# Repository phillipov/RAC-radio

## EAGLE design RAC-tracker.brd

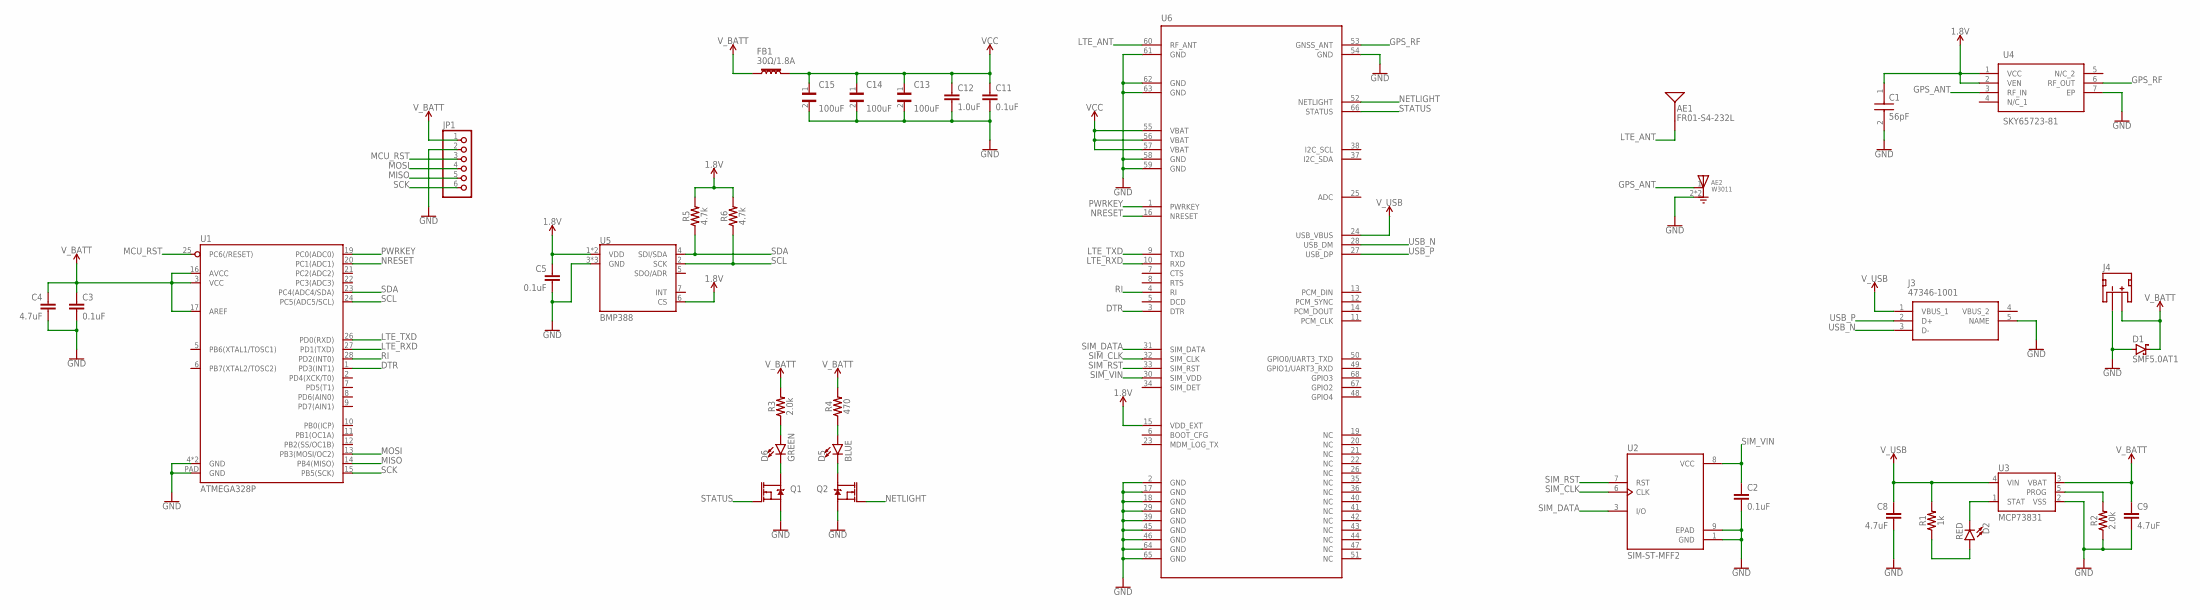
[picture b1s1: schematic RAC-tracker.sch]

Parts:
AE1: FR01-S4-232L; FR01-S4-232
AE2: W3011; XDCR_W3011
C1: 56pF; CAPC1608X90N
C2, C3, C5, C11: 0.1uF; 0603
C4, C8, C9: 4.7uF; 0603
C12: 1.0uF; 0603
C13, C14, C15: 100uF; CAPC3216X180N
D1: SMF5.0AT1; SOD123FL
D2: RED; LED-0603
D5: BLUE; LED-0603
D6: GREEN; LED-0603
FB1: 30Ω/1.8A; 0603
J3: 47346-1001; 47346-0001
J4: JST_2MM_MALE; JST-2-SMD
JP1: PINHD-1X6; 1X06
Q1, Q2: 220mA/50V/3.5Ω; SOT23-3
R1: 1k; 0603
R2, R3: 2.0k; 0603
R4: 470; 0603
R5, R6: 4.7k; 0603
U1: ATMEGA328P; VQFN-28
U2: SIM-ST-MFF2; PSON127P500X600X82-9N
U3: MCP73831; SOT23-5
U4: SKY65723-81; SKY6572381
U5: BMP388; LGA-10(2X2)
U6: SIM7000

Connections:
1.8V: C1.1, C5.1, R5.2, R6.2, U4.1 (VCC), U4.2 (VEN), U5.1 (VDD), U5.6 (CS), U5.10 (VDD), U6.15 (VDD_EXT)
DTR: U1.1 (PD3(INT1)), U6.3 (DTR)
GND: AE2.2 (GND), AE2.3 (GND), C1.2, C2.2, C3.2, C4.2, C5.2, C8.2, C9.2, C11.2, C12.2, C13.2, C14.2, C15.2, D1.A, J3.5 (NAME), J4.1 (-), JP1.2, Q1.2 (S), Q2.2 (S), R2.1, U1.4 (GND), U1.18 (GND), U1.PAD (GND), U2.1 (GND), U2.9 (EPAD), U3.2 (VSS), U4.7 (EP), U5.3 (GND), U5.8 (GND), U5.9 (GND), U6.2 (GND), U6.17 (GND), U6.18 (GND), U6.29 (GND), U6.39 (GND), U6.45 (GND), U6.46 (GND), U6.54 (GND), U6.58 (GND), U6.59 (GND), U6.61 (GND), U6.62 (GND), U6.63 (GND), U6.64 (GND), U6.65 (GND)
GPS_ANT: AE2.1 (FEED), U4.3 (RF_IN)
GPS_RF: U4.6 (RF_OUT), U6.53 (GNSS_ANT)
LED_NET_A: D5.A, R4.1
LED_NET_C: D5.C, Q2.3 (D)
LED_STAT_A: D6.A, R3.1
LED_STAT_C: D6.C, Q1.3 (D)
LTE_ANT: AE1.2, U6.60 (RF_ANT)
LTE_RXD: U1.27 (PD1(TXD)), U6.10 (RXD)
LTE_TXD: U1.26 (PD0(RXD)), U6.9 (TXD)
MCU_RST: JP1.3, U1.25 (PC6(/RESET))
MISO: JP1.5, U1.14 (PB4(MISO))
MOSI: JP1.4, U1.13 (PB3(MOSI/OC2))
NETLIGHT: Q2.1 (G), U6.52 (NETLIGHT)
NRESET: U1.20 (PC1(ADC1)), U6.16 (NRESET)
PROG: R2.2, U3.5 (PROG)
PWRKEY: U1.19 (PC0(ADC0)), U6.1 (PWRKEY)
RI: U1.28 (PD2(INT0)), U6.4 (RI)
SCK: JP1.6, U1.15 (PB5(SCK))
SCL: R6.1, U1.24 (PC5(ADC5/SCL)), U5.2 (SCK)
SDA: R5.1, U1.23 (PC4(ADC4/SDA)), U5.4 (SDI/SDA)
SIM_CLK: U2.6 (CLK), U6.32 (SIM_CLK)
SIM_DATA: U2.3 (I/O), U6.31 (SIM_DATA)
SIM_RST: U2.7 (RST), U6.33 (SIM_RST)
SIM_VIN: C2.1, U2.8 (VCC), U6.30 (SIM_VDD)
STAT: D2.C, U3.1 (STAT)
STATUS: Q1.1 (G), U6.66 (STATUS)
STAT_AN: D2.A, R1.1
USB_N: J3.3 (D-), U6.28 (USB_DM)
USB_P: J3.2 (D+), U6.27 (USB_DP)
VCC: C11.1, C12.1, C13.1, C14.1, C15.1, FB1.2, U6.55 (VBAT), U6.56 (VBAT), U6.57 (VBAT)
V_BATT: C3.1, C4.1, C9.1, D1.C, FB1.1, J4.2 (+), JP1.1, R3.2, R4.2, U1.3 (VCC), U1.16 (AVCC), U1.17 (AREF), U3.3 (VBAT)
V_USB: C8.1, J3.1 (VBUS_1), R1.2, U3.4 (VIN), U6.24 (USB_VBUS)

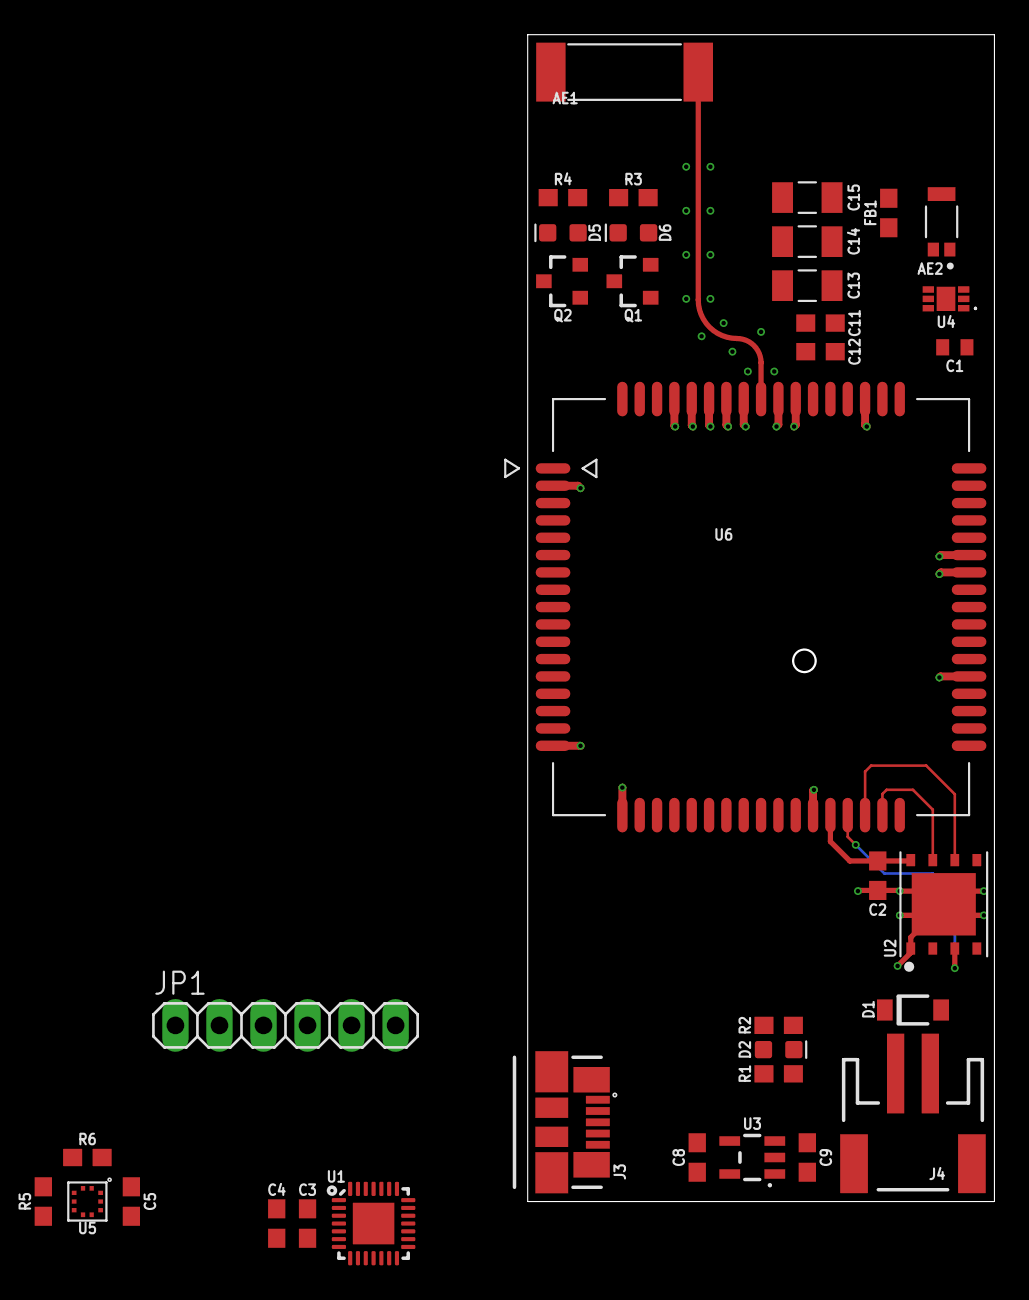
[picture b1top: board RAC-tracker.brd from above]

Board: 4 copper layers, 26.9 x 67.3 mm, 36 parts (0 on the bottom side), 35 nets.

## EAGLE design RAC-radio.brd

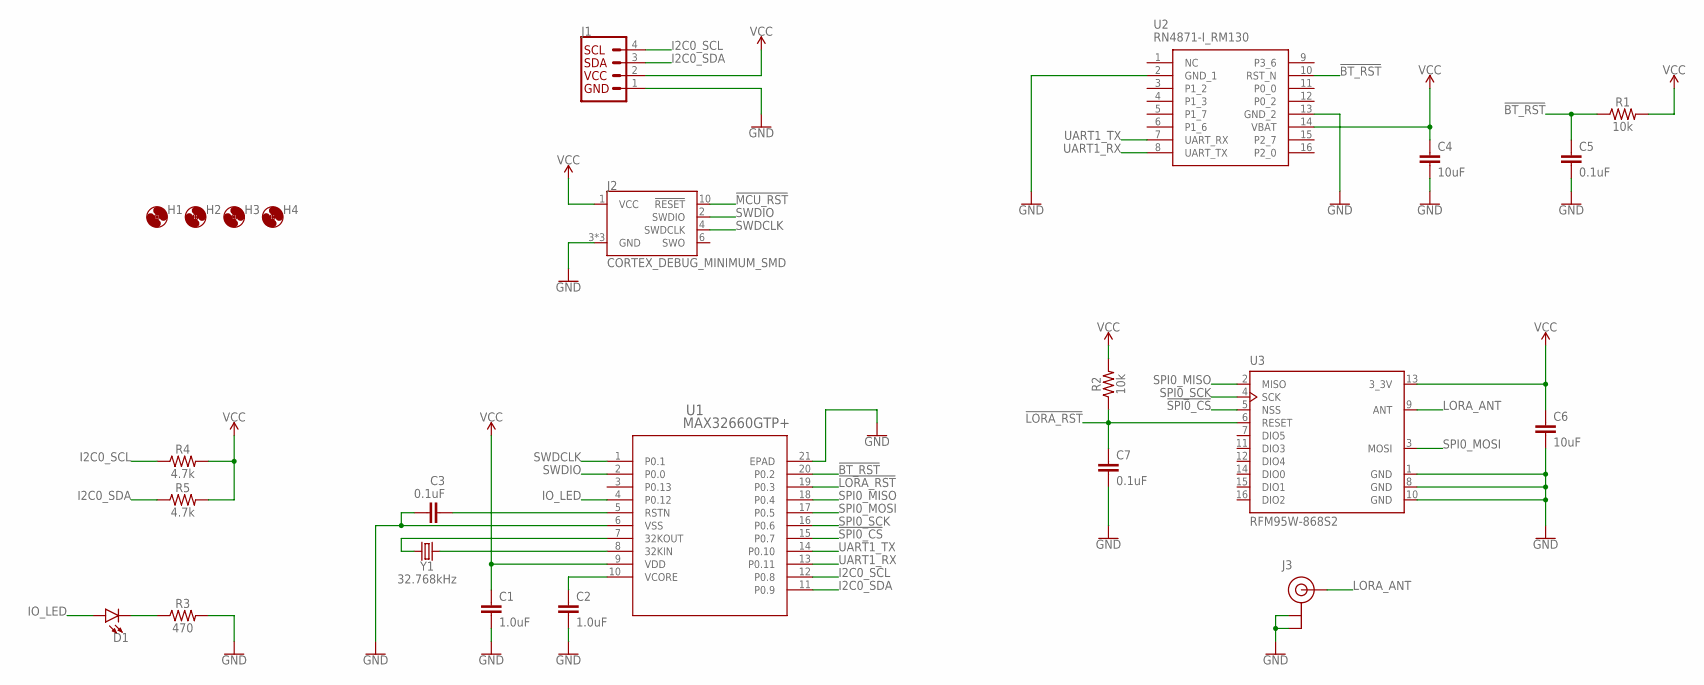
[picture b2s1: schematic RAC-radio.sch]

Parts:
C1, C2: 1.0uF; 0603
C3, C5, C7: 0.1uF; 0603
C4, C6: 10uF; 0603
D1: LED0603; LED-0603
H1, H2, H3, H4: MOUNT-HOLE2.8; 2,8
J1: QWIIC_CONNECTORJS-1MM; JST04_1MM_RA
J2: CORTEX_DEBUG_MINIMUM_SMD; SAMTECH_FTSH-105-01
J3: U.FL
R1, R2: 10k; 0603
R3: 470; 0603
R4, R5: 4.7k; 0603
U1: MAX32660GTP+; 21-0139V_T2044+5
U2: RN4871-I_RM130; RN4871
U3: RFM95W-868S2; XCVR_RFM95W-868S2
Y1: 32.768kHz; CRYSTAL-SMD-3.2X1.5MM

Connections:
32KIN: U1.8 (32KIN), Y1.P$1 (1)
32KOUT: U1.7 (32KOUT), Y1.P$2 (2)
!BT_RST: C5.1, R1.1, U1.20 (P0.2), U2.10 (RST_N)
!LORA_RST: C7.1, R2.1, U1.19 (P0.3), U3.6 (RESET)
!MCU_RST: C3.1, J2.10 (!RESET), U1.5 (RSTN)
!SPI0_CS: U1.15 (P0.7), U3.5 (NSS)
GND: C1.2, C2.2, C3.2, C4.2, C5.2, C6.2, C7.2, J1.1, J2.3 (GND), J2.5 (GND), J2.9 (GND), J3.1 (GND), J3.2 (GND), R3.2, U1.6 (VSS), U1.21 (EPAD), U2.2 (GND_1), U2.13 (GND_2), U3.1 (GND), U3.8 (GND), U3.10 (GND)
I2C0_SCL: J1.4, R4.1, U1.12 (P0.8)
I2C0_SDA: J1.3, R5.1, U1.11 (P0.9)
IO_LED: D1.A, U1.4 (P0.12)
LED_CATH: D1.C, R3.1
LORA_ANT: J3.FEED (SIGNAL), U3.9 (ANT)
SPI0_MISO: U1.18 (P0.4), U3.2 (MISO)
SPI0_MOSI: U1.17 (P0.5), U3.3 (MOSI)
SPI0_SCK: U1.16 (P0.6), U3.4 (SCK)
SWDCLK: J2.4 (SWDCLK), U1.1 (P0.1)
SWDIO: J2.2 (SWDIO), U1.2 (P0.0)
UART1_RX: U1.13 (P0.11), U2.8 (UART_TX)
UART1_TX: U1.14 (P0.10), U2.7 (UART_RX)
VCC: C1.1, C4.1, C6.1, J1.2, J2.1 (VCC), R1.2, R2.2, R4.2, R5.2, U1.9 (VDD), U2.14 (VBAT), U3.13 (3_3V)
VCORE: C2.1, U1.10 (VCORE)

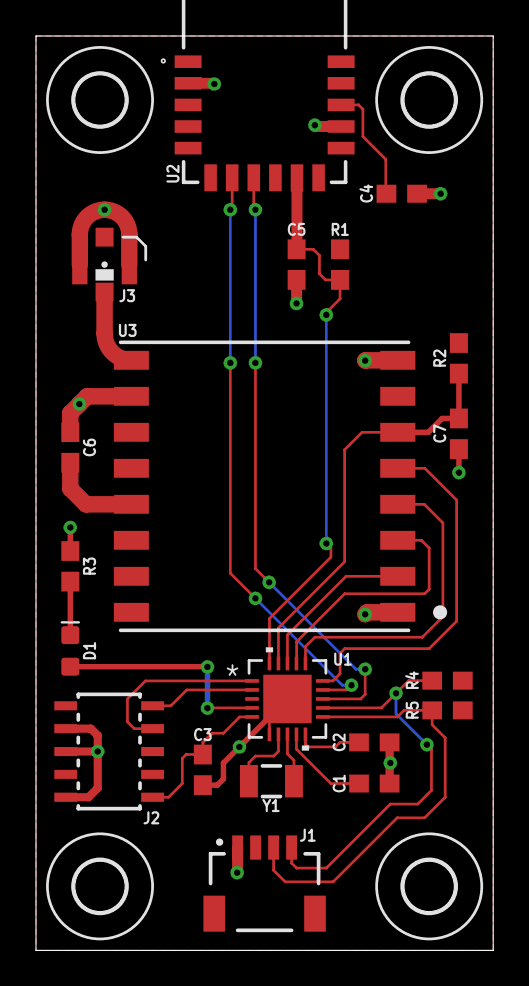
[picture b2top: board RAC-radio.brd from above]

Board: 2 copper layers, 25.4 x 50.8 mm, 24 parts (0 on the bottom side), 21 nets.

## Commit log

2019-08-25 Integrated MCU, BLE, and LoRa subsystems
2019-08-25 Started a board file
2019-08-26 Routed the non-power nets
2019-08-26 Finished routing board, cleared DRC
2019-12-17 Started anew with the SIM7000 LTE-M/GPS module
2019-12-17 renamed files to reflect change in purpose from radio telemetry to location tracking
2019-12-18 Started connecting the SIM7000
2019-12-26 Added LiPo charging circuit, LiPo connector, and USB connector
2019-12-26 Renamed nets and started board placement
2019-12-29 Added GPS frontend, further integrated NRF9160
2019-12-30 Replaced GPS front-end, added 1.8V LDO
2019-12-30 Fixed missing LDO nets, started routing board
2020-01-04 Completed routing, cleared DRC errors
2020-01-06 Stitched vias in the top ground plane. Ready for fabrication!
2020-01-06 Added a purchasable Molex Micro-USB connector
2020-01-06 U.FL replaced to fit BOM, polygons adjusted. Fab ready!
2020-02-07 Starting again with the SIM7000
2020-02-08 Set up minimum schematic for SIM7000
2020-02-17 Replaced u.FL connectors with SMD antennas
2020-02-18 Added ATMEGA328P and BMP388 to schematic, likely won't keep

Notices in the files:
parts and their libraries:
SparkFun-Capacitors: Licensing: Creative Commons ShareAlike 4.0 International - https://creativecommons.org/licenses/by-sa/4.0
